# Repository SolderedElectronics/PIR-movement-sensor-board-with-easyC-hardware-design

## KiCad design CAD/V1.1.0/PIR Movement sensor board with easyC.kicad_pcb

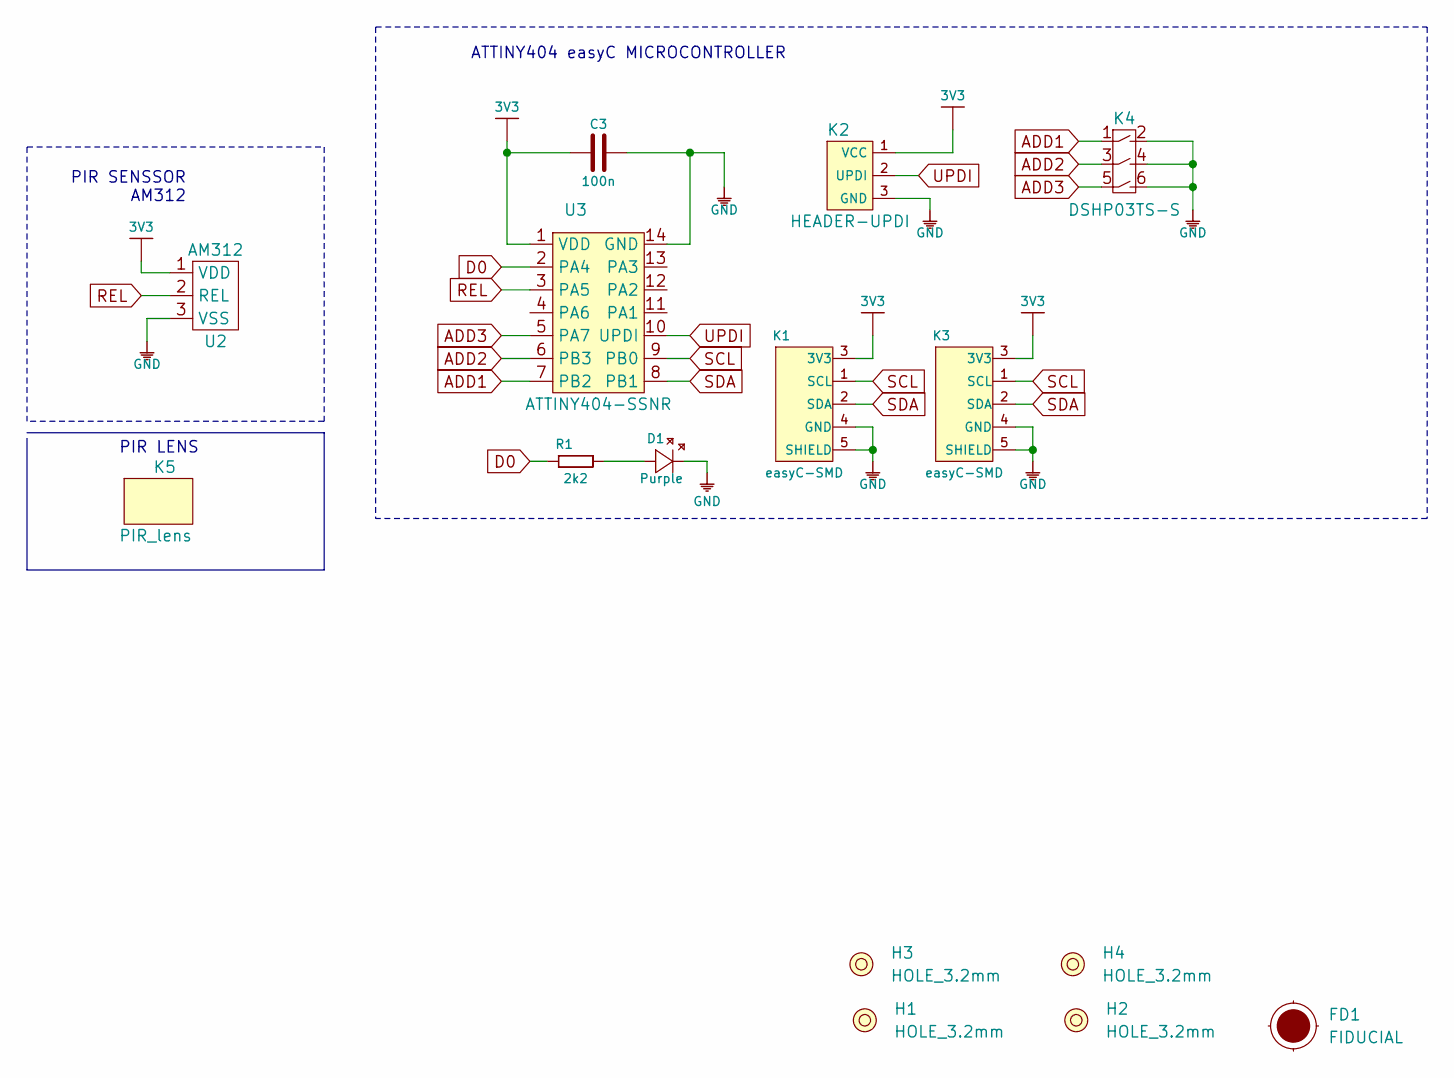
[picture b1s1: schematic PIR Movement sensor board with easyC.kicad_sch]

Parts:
C3: 100n; 0603C
D1: Purple; 0402LED
FD1: FIDUCIAL; FIDUCIAL_23
H1, H2, H3, H4: HOLE_3.2mm
K1, K3: easyC-SMD; easyC-connector
K2: HEADER-UPDI
K4: DSHP03TS-S
K5: PIR_lens; PIR_senzor_kapica
R1: 2k2; 0402R
U2: AM312; PIR_senzor
U3: ATTINY404-SSNR; SOIC-14

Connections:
3V3: C3.1, K1.3 (3V3), K2.1 (VCC), K3.3 (3V3), U2.1 (VDD), U3.1 (VDD)
ADD1: K4.1, U3.7 (PB2)
ADD2: K4.3, U3.6 (PB3)
ADD3: K4.5, U3.5 (PA7)
D0: R1.1, U3.2 (PA4)
GND: C3.2, D1.2 (K), K1.4 (GND), K1.5 (SHIELD), K2.3 (GND), K3.4 (GND), K3.5 (SHIELD), K4.2, K4.4, K4.6, U2.3 (VSS), U3.14 (GND)
unnamed: D1.1 (A), R1.2
REL: U2.2 (REL), U3.3 (PA5)
SCL: K1.1 (SCL), K3.1 (SCL), U3.9 (PB0)
SDA: K1.2 (SDA), K3.2 (SDA), U3.8 (PB1)
UPDI: K2.2 (UPDI), U3.10 (UPDI)

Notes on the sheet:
ATTINY404 easyC MICROCONTROLLER
PIR LENS
PIR SENSSOR AM312

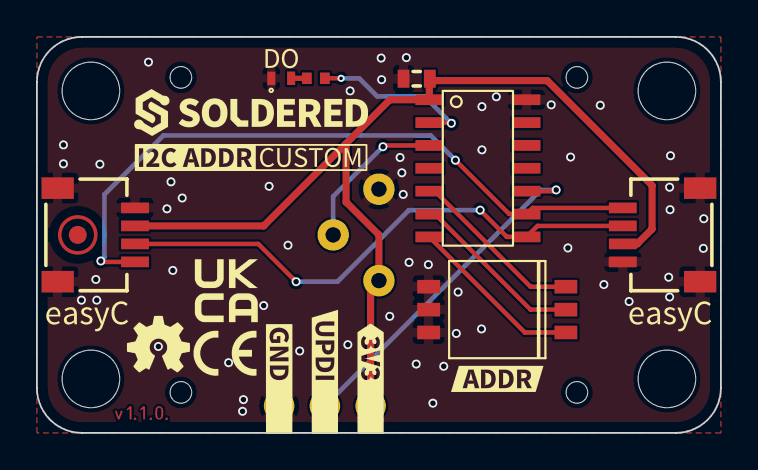
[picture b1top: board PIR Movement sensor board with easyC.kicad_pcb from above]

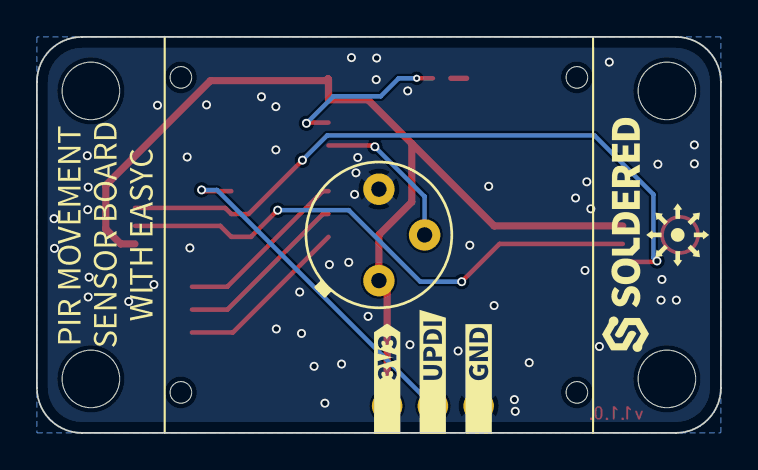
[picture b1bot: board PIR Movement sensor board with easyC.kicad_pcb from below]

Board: 2 copper layers, 38.0 x 22.0 mm, 27 parts (8 on the bottom side), 11 nets.

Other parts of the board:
Ref**: Val**; Version1.1.0
kibuzzard-641181E6: G***; kibuzzard-641181E6
kibuzzard-641185A3: G***; kibuzzard-641185A3
kibuzzard-6411825C: G***; kibuzzard-6411825C
kibuzzard-64118155: G***; kibuzzard-64118155
kibuzzard-64118187: G***; kibuzzard-64118187
kibuzzard-64118214: G***; kibuzzard-64118214
kibuzzard-64118226: G***; kibuzzard-64118226
kibuzzard-64118254: G***; kibuzzard-64118254
kibuzzard-64118262: G***; kibuzzard-64118262
kibuzzard-64118455: G***; kibuzzard-64118455
kibuzzard-64118594: G***; kibuzzard-64118594

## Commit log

2022-08-06 Updating open source files.
